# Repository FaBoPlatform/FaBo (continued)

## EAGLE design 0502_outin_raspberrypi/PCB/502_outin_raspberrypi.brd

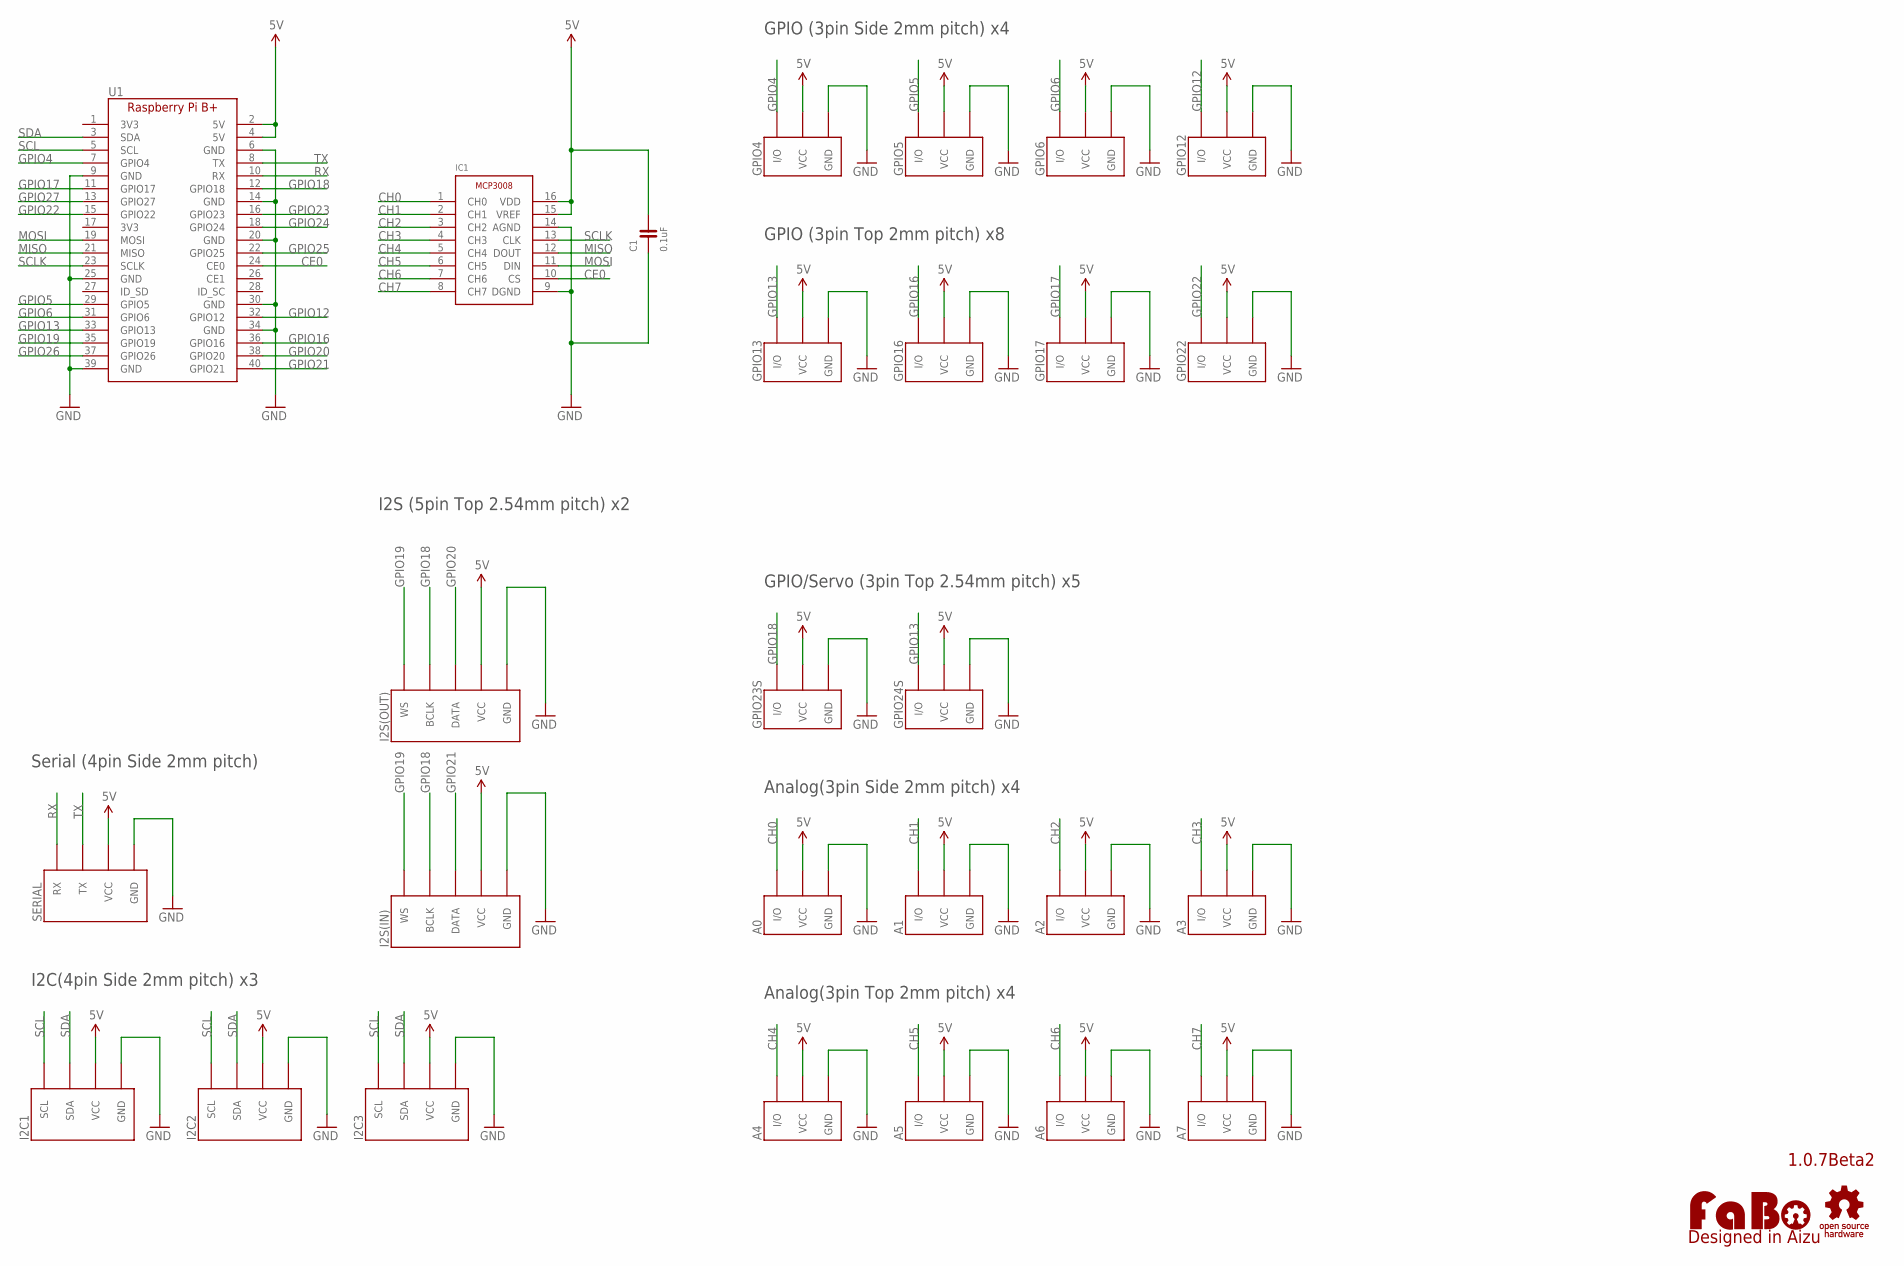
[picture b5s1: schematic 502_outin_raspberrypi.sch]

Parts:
A0, A1, A2, A3: FABO_BRICK_3PIN-S03B-PASK-2; FABO_BRICK_3PIN_S03B-PASK-2
A4, A5, A6, A7: FABO_BRICK_3PIN-B03B-PASK-1; FABO_BRICK_3PIN_B03B-PASK-1
C1: 0.1uF; 0603
GPIO4, GPIO5, GPIO6, GPIO12: FABO_BRICK_3PIN-S03B-PASK-2; FABO_BRICK_3PIN_S03B-PASK-2
GPIO13, GPIO16, GPIO17, GPIO22: FABO_BRICK_3PIN-B03B-PASK-1; FABO_BRICK_3PIN_B03B-PASK-1
GPIO23S, GPIO24S: FABO_BRICK_3PIN-HEADER; FABO_BRICK_3PIN_HEADER
I2C1, I2C2, I2C3: FABO_BRICK_I2C-S04B-PASK-2; FABO_BRICK_I2C_S04B-PASK-2
I2S(IN), I2S(OUT): FABO_BRICK_I2SLONG; FABO_BRICK_I2S_S05B-PASK-2_LONG
IC1: MICROCHIP-MCP3008
LOGO1: LOGO_FABO-M; LOGO_FABO_M
SERIAL: FABO_BRICK_SERIAL-S04B-PASK-2; FABO_BRICK_SERIAL_S04B-PASK-2
U1: RASPBERRY_PI_B+
U$4: LOGO_OSHW-T_M_BOTTOM; LOGO_OSHW_T_MS_BOTTOM

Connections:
5V: A0.VCC, A1.VCC, A2.VCC, A3.VCC, A4.VCC, A5.VCC, A6.VCC, A7.VCC, C1.2, GPIO4.VCC, GPIO5.VCC, GPIO6.VCC, GPIO12.VCC, GPIO13.VCC, GPIO16.VCC, GPIO17.VCC, GPIO22.VCC, GPIO23S.VCC, GPIO24S.VCC, I2C1.VCC, I2C2.VCC, I2C3.VCC, I2S(IN).VCC, I2S(OUT).VCC, IC1.15 (VREF), IC1.16 (VDD), SERIAL.VCC, U1.2 (5V), U1.4 (5V)
CE0: IC1.10 (CS), U1.24 (CE0)
CH0: A0.I/O, IC1.1 (CH0)
CH1: A1.I/O, IC1.2 (CH1)
CH2: A2.I/O, IC1.3 (CH2)
CH3: A3.I/O, IC1.4 (CH3)
CH4: A4.I/O, IC1.5 (CH4)
CH5: A5.I/O, IC1.6 (CH5)
CH6: A6.I/O, IC1.7 (CH6)
CH7: A7.I/O, IC1.8 (CH7)
GND: A0.GND, A1.GND, A2.GND, A3.GND, A4.GND, A5.GND, A6.GND, A7.GND, C1.1, GPIO4.GND, GPIO5.GND, GPIO6.GND, GPIO12.GND, GPIO13.GND, GPIO16.GND, GPIO17.GND, GPIO22.GND, GPIO23S.GND, GPIO24S.GND, I2C1.GND, I2C2.GND, I2C3.GND, I2S(IN).GND, I2S(OUT).GND, IC1.9 (DGND), IC1.14 (AGND), SERIAL.GND, U1.6 (GND), U1.9 (GND), U1.14 (GND), U1.20 (GND), U1.25 (GND), U1.30 (GND), U1.34 (GND), U1.39 (GND)
GPIO4: GPIO4.I/O, U1.7 (GPIO4)
GPIO5: GPIO5.I/O, U1.29 (GPIO5)
GPIO6: GPIO6.I/O, U1.31 (GPIO6)
GPIO12: GPIO12.I/O, U1.32 (GPIO12)
GPIO13: GPIO13.I/O, GPIO24S.I/O, U1.33 (GPIO13)
GPIO16: GPIO16.I/O, U1.36 (GPIO16)
GPIO17: GPIO17.I/O, U1.11 (GPIO17)
GPIO18: GPIO23S.I/O, I2S(IN).BCLK, I2S(OUT).BCLK, U1.12 (GPIO18)
GPIO19: I2S(IN).WS, I2S(OUT).WS, U1.35 (GPIO19)
GPIO20: I2S(OUT).DATA, U1.38 (GPIO20)
GPIO21: I2S(IN).DATA, U1.40 (GPIO21)
GPIO22: GPIO22.I/O, U1.15 (GPIO22)
GPIO23: U1.16 (GPIO23)
GPIO24: U1.18 (GPIO24)
GPIO25: U1.22 (GPIO25)
GPIO26: U1.37 (GPIO26)
GPIO27: U1.13 (GPIO27)
MISO: IC1.12 (DOUT), U1.21 (MISO)
MOSI: IC1.11 (DIN), U1.19 (MOSI)
RX: SERIAL.RX, U1.10 (RX)
SCL: I2C1.SCL, I2C2.SCL, I2C3.SCL, U1.5 (SCL)
SCLK: IC1.13 (CLK), U1.23 (SCLK)
SDA: I2C1.SDA, I2C2.SDA, I2C3.SDA, U1.3 (SDA)
TX: SERIAL.TX, U1.8 (TX)

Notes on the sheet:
1.0.7Beta2
GPIO (3pin Side 2mm pitch) x4
I2C(4pin Side 2mm pitch) x3
Analog(3pin Side 2mm pitch) x4
Serial (4pin Side 2mm pitch)
GPIO (3pin Top 2mm pitch) x8
GPIO/Servo (3pin Top 2.54mm pitch) x5
Analog(3pin Top 2mm pitch) x4
I2S (5pin Top 2.54mm pitch) x2

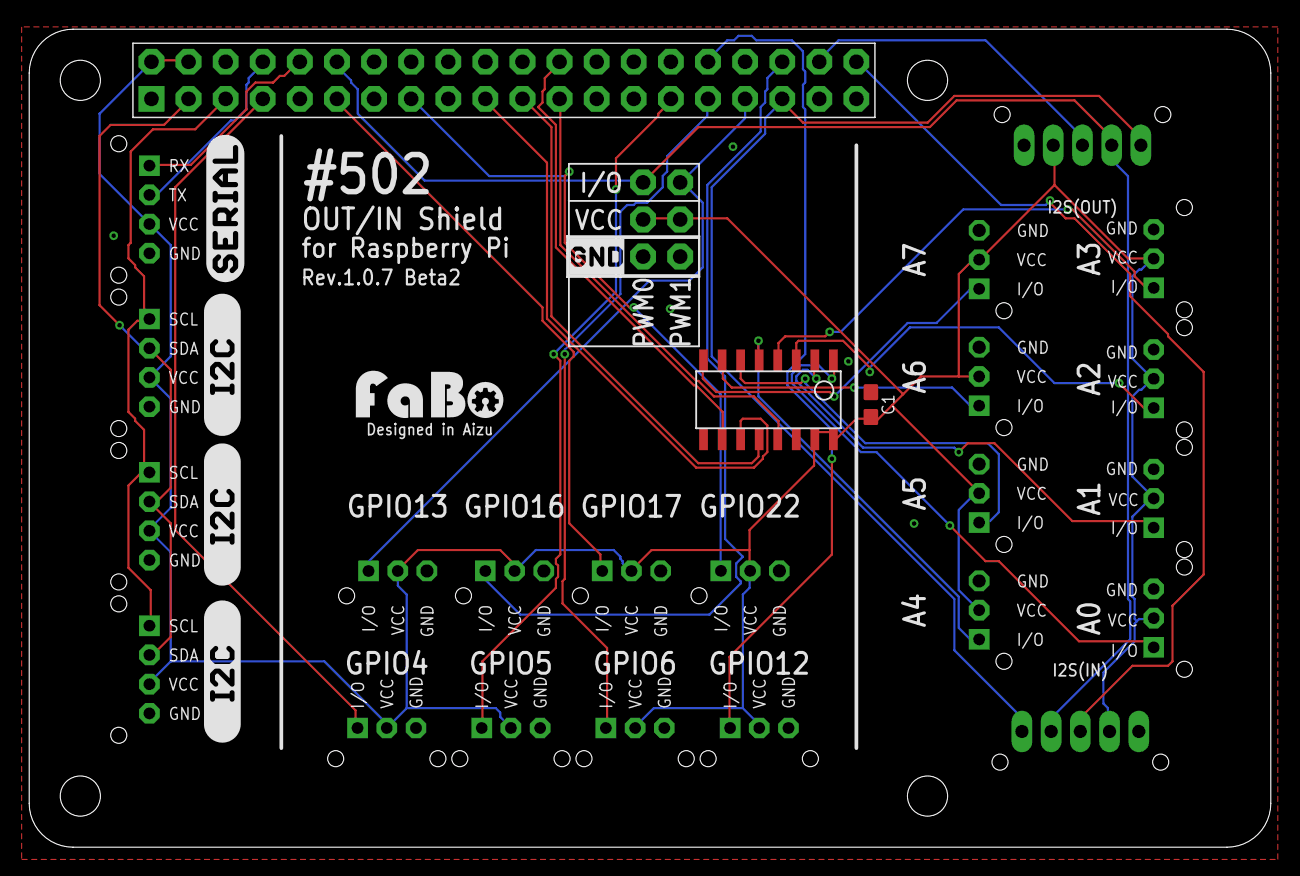
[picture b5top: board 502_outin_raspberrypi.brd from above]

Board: 2 copper layers, 85.0 x 56.0 mm, 34 parts (0 on the bottom side), 30 nets.

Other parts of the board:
U$2, U$5, U$6: LOGO_SILK_I2C
U$3: LOGO_SILK_SERIAL2
U$7: LOGO_SILK_GND

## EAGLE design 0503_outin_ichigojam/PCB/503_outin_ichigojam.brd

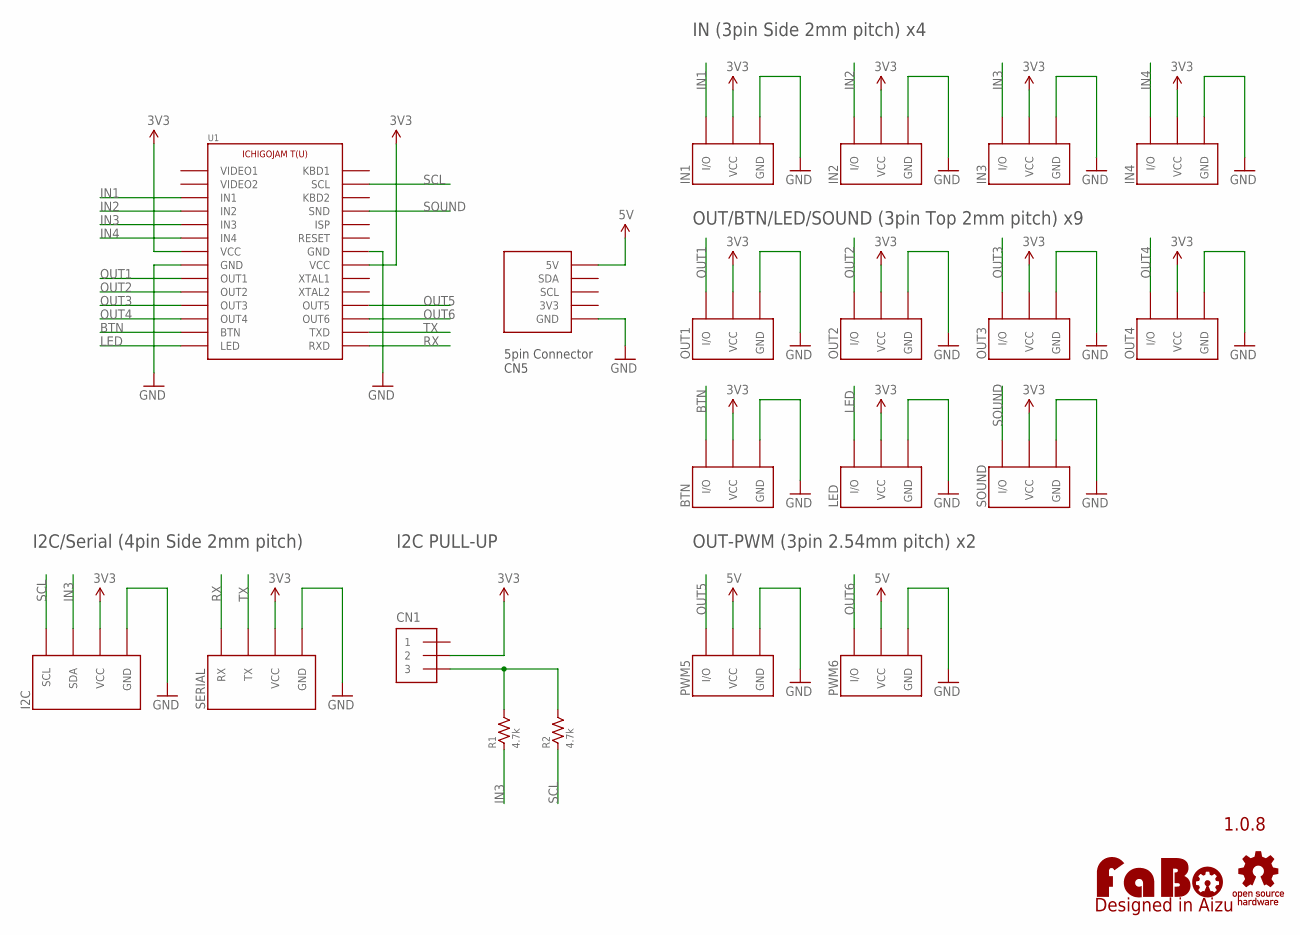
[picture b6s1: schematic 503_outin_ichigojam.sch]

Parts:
BTN: FABO_BRICK_3PIN-B03B-PASK-1; FABO_BRICK_3PIN_B03B-PASK-1
CN1: PIN_HEADER_1X3; PIN_1X3
I2C: FABO_BRICK_I2C-S04B-PASK-2_LONG; FABO_BRICK_I2C_S04B-PASK-2_LONG
IN1, IN2, IN3, IN4: FABO_BRICK_3PIN-S03B-PASK-2_LONG; FABO_BRICK_3PIN_S03B-PASK-2_LONG
LED: FABO_BRICK_3PIN-B03B-PASK-1; FABO_BRICK_3PIN_B03B-PASK-1
LOGO1: LOGO_FABO-M; LOGO_FABO_M
OUT1, OUT2, OUT3, OUT4: FABO_BRICK_3PIN-B03B-PASK-1; FABO_BRICK_3PIN_B03B-PASK-1
PWM5, PWM6: FABO_BRICK_3PIN-HEADER; FABO_BRICK_3PIN_HEADER
R1, R2: 4.7k; AXL-REGULAR
SERIAL: FABO_BRICK_SERIAL-S04B-PASK-2_LONG; FABO_BRICK_SERIAL_S04B-PASK-2_LONG
SOUND: FABO_BRICK_3PIN-B03B-PASK-1; FABO_BRICK_3PIN_B03B-PASK-1
U1: ICHIGOJAM_T-NOLABEL; ICHIGOJAM_T_NOLABEL
U$2: LOGO_OSHW-M_BOTTOM; LOGO_OSHW_M_BOTTOM

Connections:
3V3: BTN.VCC, CN1.2, I2C.VCC, IN1.VCC, IN2.VCC, IN3.VCC, IN4.VCC, LED.VCC, OUT1.VCC, OUT2.VCC, OUT3.VCC, OUT4.VCC, SERIAL.VCC, SOUND.VCC, U1.VCC1 (VCC), U1.VCC2 (VCC)
5V: PWM5.VCC, PWM6.VCC, U1.5V
BTN: BTN.I/O, U1.BTN
GND: BTN.GND, I2C.GND, IN1.GND, IN2.GND, IN3.GND, IN4.GND, LED.GND, OUT1.GND, OUT2.GND, OUT3.GND, OUT4.GND, PWM5.GND, PWM6.GND, SERIAL.GND, SOUND.GND, U1.GND1 (GND), U1.GND2 (GND), U1.GND3 (GND)
IN1: IN1.I/O, U1.IN1
IN2: IN2.I/O, U1.IN2
IN3: I2C.SDA, IN3.I/O, R1.1, U1.IN3
IN4: IN4.I/O, U1.IN4
LED: LED.I/O, U1.LED
unnamed: CN1.3, R1.2, R2.2
OUT1: OUT1.I/O, U1.OUT1
OUT2: OUT2.I/O, U1.OUT2
OUT3: OUT3.I/O, U1.OUT3
OUT4: OUT4.I/O, U1.OUT4
OUT5: PWM5.I/O, U1.OUT5
OUT6: PWM6.I/O, U1.OUT6
RX: SERIAL.RX, U1.RXD
SCL: I2C.SCL, R2.1, U1.SCL1 (SCL)
SOUND: SOUND.I/O, U1.SND
TX: SERIAL.TX, U1.TXD

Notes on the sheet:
1.0.8
IN (3pin Side 2mm pitch) x4
OUT/BTN/LED/SOUND (3pin Top 2mm pitch) x9
I2C/Serial (4pin Side 2mm pitch)
I2C PULL-UP
5pin Connector CN5
OUT-PWM (3pin 2.54mm pitch) x2

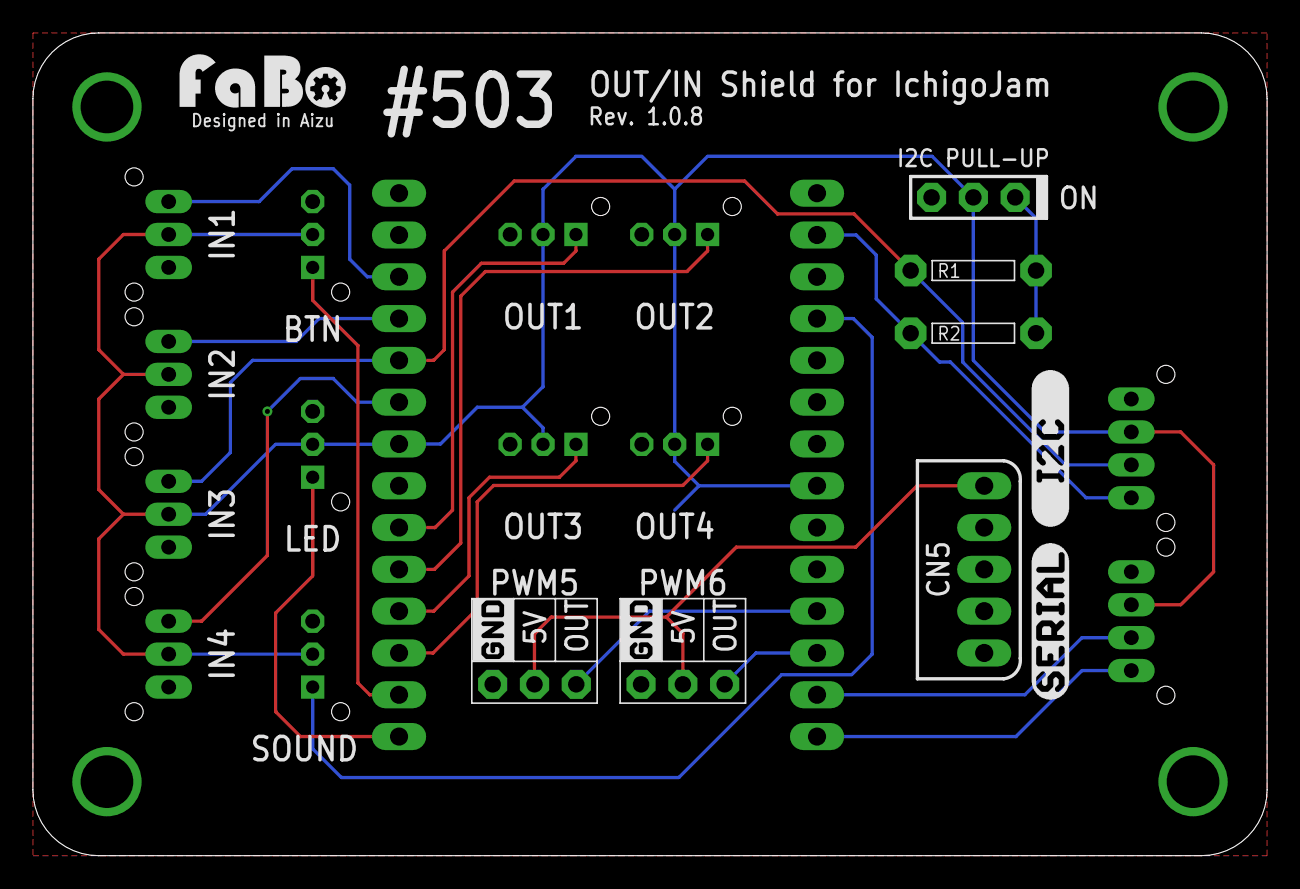
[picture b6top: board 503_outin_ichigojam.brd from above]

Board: 2 copper layers, 75.0 x 50.0 mm, 25 parts (0 on the bottom side), 20 nets.

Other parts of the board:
U$4: LOGO_SILK_I2C
U$5: LOGO_SILK_SERIAL2
U$7, U$8: LOGO_SILK_GND
